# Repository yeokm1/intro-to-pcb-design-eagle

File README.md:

# intro-to-pcb-design

A class to introduce students to designing Printed Circuit Boards (PCBs) using the Eagle software. The PCB that will be designed is based on a 555 Timer circuit. Reflow soldering with stencil and solder paste will also be covered. 

The lesson should take approximately 6 hours to complete.

My slides are available on slideshare using the picture link below.

#Images

Reference PCB with all components populated.

Bare PCB

Reference schematic

Reference board

#Parts/Equipment Required
1. PCB bill-of-materials (BOM) can be obtained from the [555-blinker-bom.ods spreadsheet](555-blinker-bom.ods)
2. Soldering iron
3. Reflow oven or hot-plate

#PCB Design software and addons/references used

1. Eagle 7.5.0: I use Standard but Light should still be able to open/modify the files.
2. Modified CR2032 library based on [here](https://github.com/nickaknudson/eagle-nickaknudson/blob/master/cr2032.lbr)
3. Elecrow Design Rule Check for 2 layers (in repo as `Elecrow_2-layer_eagle_rule.dru`)
4. Elecrow Gerber Generater 2-layer board (in repo as `Elecrow_Gerber_Generater_DrillAlign.cam`)
5. [Seeed OPL libraries](http://www.seeedstudio.com/wiki/File:OPL_eagle_library.zip)
6. [Sparkfun Electromechanical](https://github.com/sparkfun/SparkFun-Eagle-Libraries/)
7. [bt_regulator](https://github.com/shimniok/eagle-library/blob/master/bt_regulator.lbr)

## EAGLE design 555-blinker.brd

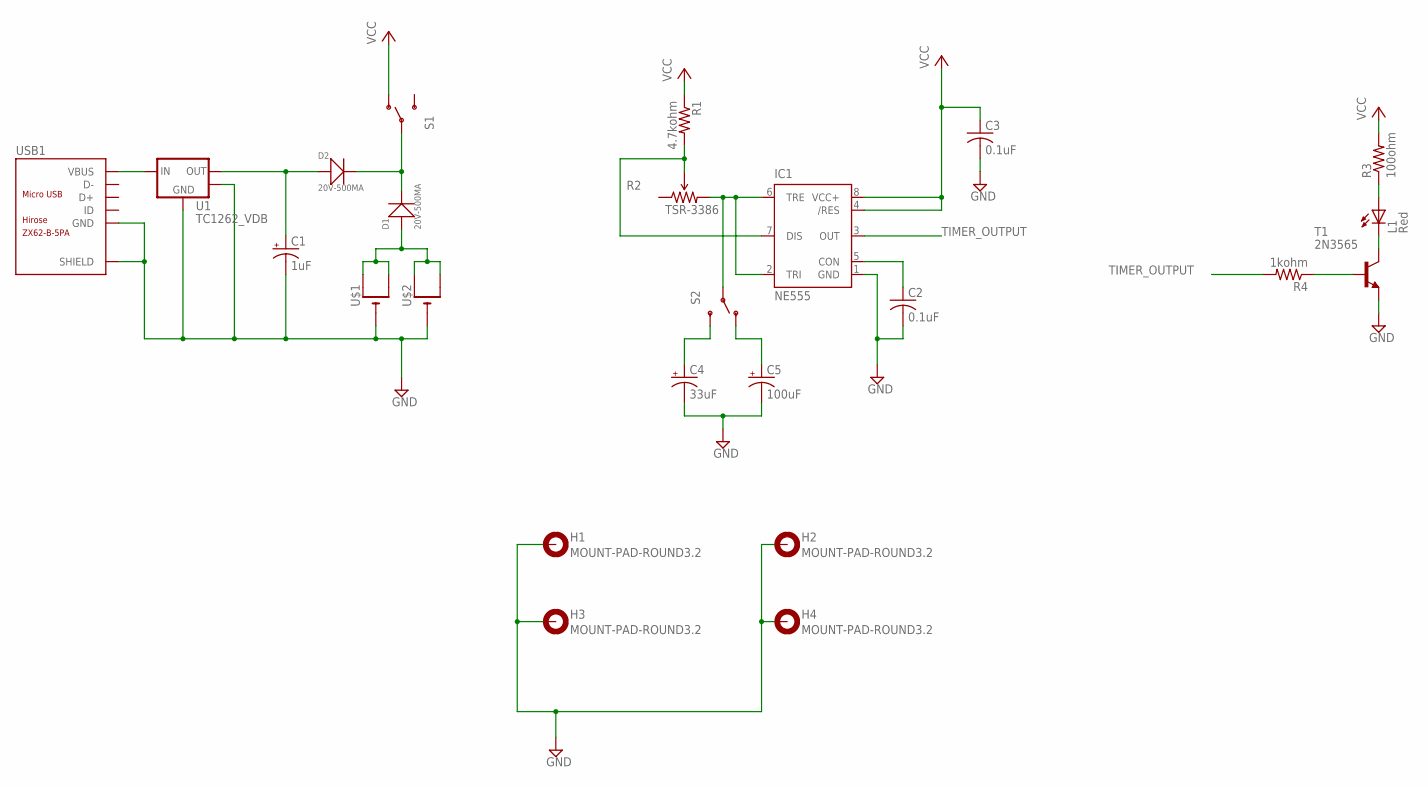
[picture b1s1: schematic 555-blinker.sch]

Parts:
C1: 1uF; UD-4X5,8_NICHICON
C2, C3: 0.1uF; C025-025X050
C4: 33uF; E2-5
C5: 100uF; E2-5
D1, D2: 20V-500MA; SOD-123
H1, H2, H3, H4: MOUNT-PAD-ROUND3.2; 3,2-PAD
IC1: NE555; DIL-08
L1: Red; LED5MM
R1: 4.7kohm; 0207/10
R2: TSR-3386; 3386U
R3: 100ohm; 0207/10
R4: 1kohm; 0207/10
S1, S2: SWITCH-SPDTPTH; SWITCH-SPDT
T1: 2N3565; TO92
U1: TC1262_VDB; SOT-223-3
U$1, U$2: CR2032SMT; CR2032-SMD
USB1: ZX62-B-5PA; MICRO-USB5+6P-SMD-0.65-AB

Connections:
GND: C1.-, C2.2, C3.2, C4.-, C5.-, H1.B3,2, H2.B3,2, H3.B3,2, H4.B3,2, IC1.1 (GND), T1.3 (E), U1.2 (GND), U1.4 (TAB), U$1.-, U$2.-, USB1.5 (GND), USB1.P1 (SHIELD), USB1.P2 (SHIELD), USB1.P3 (SHIELD), USB1.P4 (SHIELD), USB1.P5 (SHIELD), USB1.P6 (SHIELD)
unnamed: C1.+, D2.+, U1.3 (VOUT)
unnamed: D1.+, U$1.+$1 (+), U$1.+$2 (+1), U$2.+$1 (+), U$2.+$2 (+1)
unnamed: C2.1, IC1.5 (CON)
unnamed: D1.-, D2.-, S1.2
unnamed: IC1.7 (DIS), R1.2, R2.2 (WIPER)
unnamed: L1.K (C), T1.1 (C)
unnamed: L1.A, R3.1
unnamed: IC1.2 (TRI), IC1.6 (TRE), R2.3 (CW), S2.2
unnamed: R4.1, T1.2 (B)
unnamed: C4.+, S2.3 (S)
unnamed: C5.+, S2.1 (O)
TIMER_OUTPUT: IC1.3 (OUT), R4.2
VBUS: U1.1 (VIN), USB1.1 (VBUS)
VCC: C3.1, IC1.4 (/RES), IC1.8 (VCC+), R1.1, R3.2, S1.1 (O)

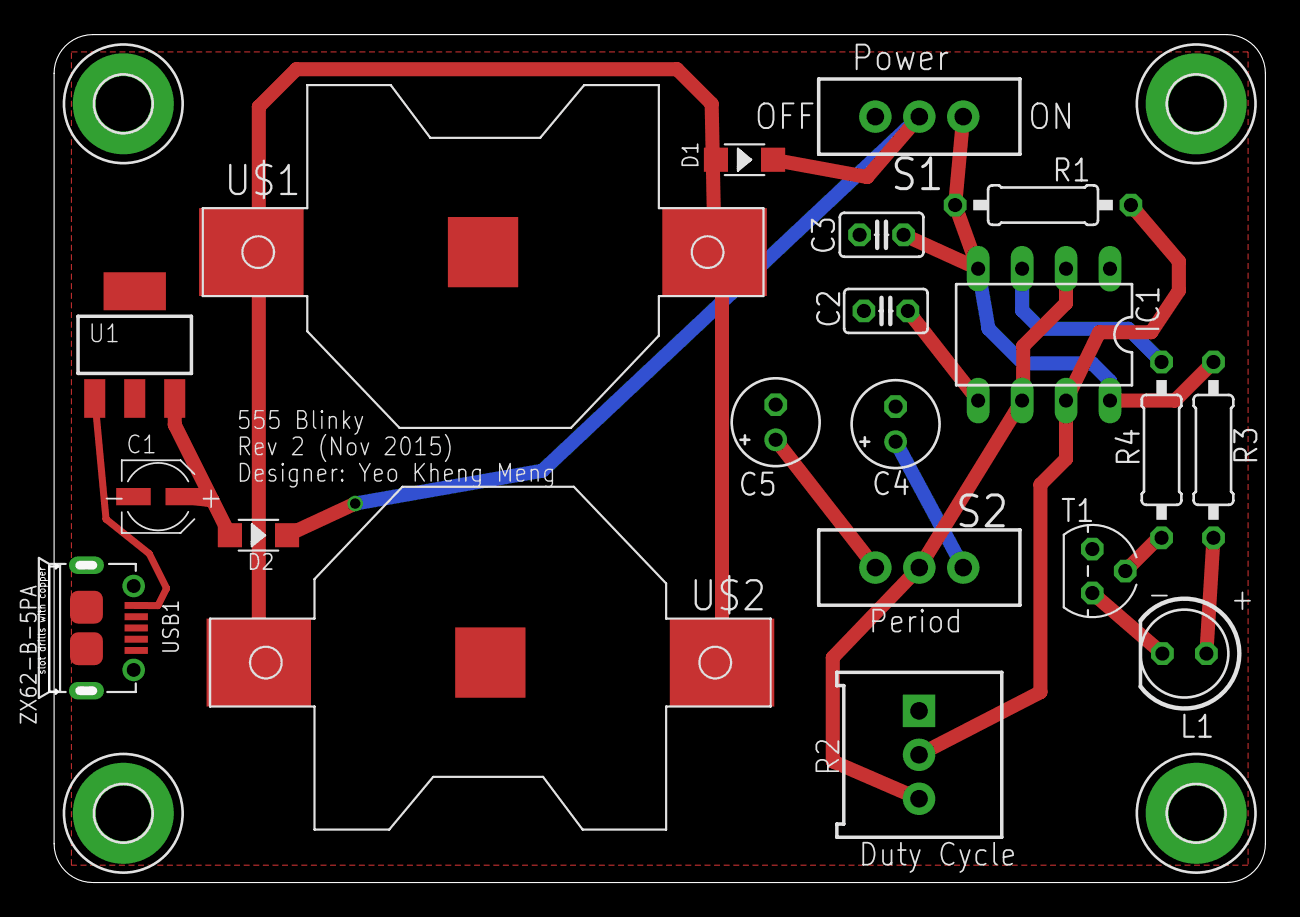
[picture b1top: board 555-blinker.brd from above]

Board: 2 copper layers, 70.0 x 49.0 mm, 24 parts (0 on the bottom side), 15 nets.

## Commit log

2016-04-16 at my web link for DIY PCB

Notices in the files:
parts and their libraries:
SparkFun-Electromechanical: Licensing: Creative Commons ShareAlike 4.0 International - https://creativecommons.org/licenses/by-sa/4.0
